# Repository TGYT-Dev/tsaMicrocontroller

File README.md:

a wearable project for TSA microcontroller project

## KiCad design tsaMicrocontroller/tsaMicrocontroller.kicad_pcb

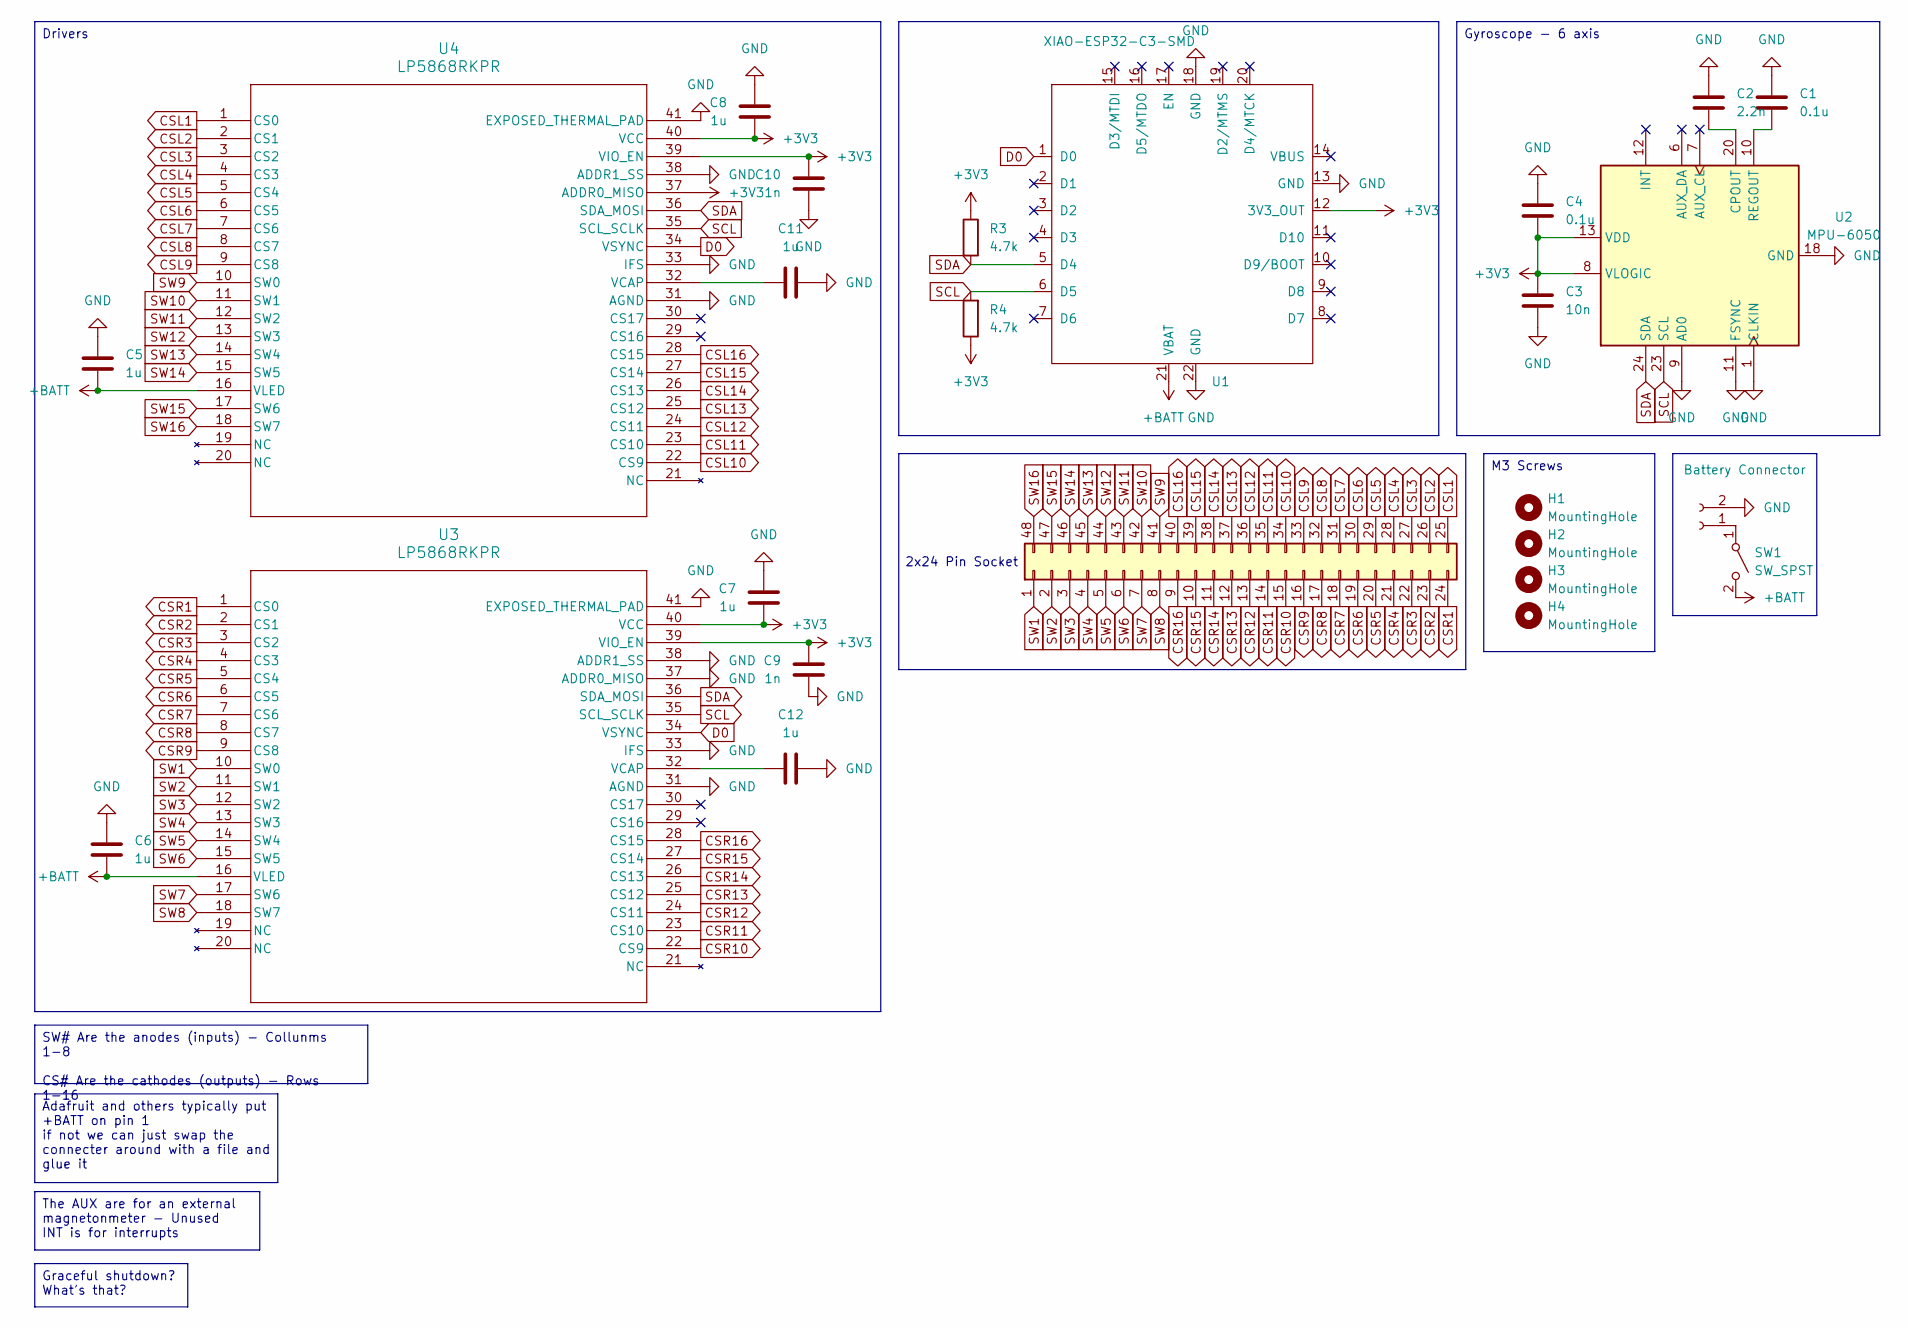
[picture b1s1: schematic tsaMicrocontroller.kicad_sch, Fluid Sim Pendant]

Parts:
C1, C4: 0.1u; C_01005_0402Metric
C2: 2.2n; C_01005_0402Metric
C3: 10n; C_01005_0402Metric
C5, C6, C7, C8, C11, C12: 1u; C_01005_0402Metric
C9, C10: 1n; C_01005_0402Metric
H1, H2, H3, H4: MountingHole; MountingHole_3.2mm_M3
J1: Battery Connector; JST_PH_S2B-PH-K_1x02_P2.00mm_Horizontal
J2: Conn_02x24_Counter_Clockwise; PinSocket_2x24_P2.54mm_Vertical
R3, R4: 4.7k; R_0201_0603Metric_Pad0.64x0.40mm_HandSolder
SW1: SW_SPST; SW_DIP_SPSTx01_Slide_6.7x4.1mm_W6.73mm_P2.54mm_LowProfile_J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
U1: XIAO-ESP32-C3-SMD; MCU_Seeed_ESP32C3
U2: MPU-6050; InvenSense_QFN-24_4x4mm_P0.5mm
U3, U4: LP5868RKPR; VQFN40-RKP_TEX

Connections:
+3V3: C3.1, C4.2, C7.2, C8.2, C9.2, C10.2, R3.1, R4.1, U1.12 (3V3_OUT), U2.8 (VLOGIC), U2.13 (VDD), U3.39 (VIO_EN), U3.40 (VCC), U4.37 (ADDR0_MISO), U4.39 (VIO_EN), U4.40 (VCC)
+BATT: C5.2, C6.2, SW1.2 (B), U1.21 (VBAT), U3.16 (VLED), U4.16 (VLED)
CSL1: J2.25, U4.1 (CS0)
CSL2: J2.26, U4.2 (CS1)
CSL3: J2.27, U4.3 (CS2)
CSL4: J2.28, U4.4 (CS3)
CSL5: J2.29, U4.5 (CS4)
CSL6: J2.30, U4.6 (CS5)
CSL7: J2.31, U4.7 (CS6)
CSL8: J2.32, U4.8 (CS7)
CSL9: J2.33, U4.9 (CS8)
CSL10: J2.34, U4.22 (CS9)
CSL11: J2.35, U4.23 (CS10)
CSL12: J2.36, U4.24 (CS11)
CSL13: J2.37, U4.25 (CS12)
CSL14: J2.38, U4.26 (CS13)
CSL15: J2.39, U4.27 (CS14)
CSL16: J2.40, U4.28 (CS15)
CSR1: J2.24, U3.1 (CS0)
CSR2: J2.23, U3.2 (CS1)
CSR3: J2.22, U3.3 (CS2)
CSR4: J2.21, U3.4 (CS3)
CSR5: J2.20, U3.5 (CS4)
CSR6: J2.19, U3.6 (CS5)
CSR7: J2.18, U3.7 (CS6)
CSR8: J2.17, U3.8 (CS7)
CSR9: J2.16, U3.9 (CS8)
CSR10: J2.15, U3.22 (CS9)
CSR11: J2.14, U3.23 (CS10)
CSR12: J2.13, U3.24 (CS11)
CSR13: J2.12, U3.25 (CS12)
CSR14: J2.11, U3.26 (CS13)
CSR15: J2.10, U3.27 (CS14)
CSR16: J2.9, U3.28 (CS15)
D0: U1.1 (D0), U3.34 (VSYNC), U4.34 (VSYNC)
GND: C1.1, C2.1, C3.2, C4.1, C5.1, C6.1, C7.1, C8.1, C9.1, C10.1, C11.1, C12.1, J1.2, U1.13 (GND), U1.18 (GND), U1.22 (GND), U2.1 (CLKIN), U2.9 (AD0), U2.11 (FSYNC), U2.18 (GND), U3.31 (AGND), U3.33 (IFS), U3.37 (ADDR0_MISO), U3.38 (ADDR1_SS), U3.41 (EXPOSED_THERMAL_PAD), U4.31 (AGND), U4.33 (IFS), U4.38 (ADDR1_SS), U4.41 (EXPOSED_THERMAL_PAD)
unnamed: J1.1, SW1.1 (A)
unnamed: C2.2, U2.20 (CPOUT)
unnamed: C1.2, U2.10 (REGOUT)
unnamed: C12.2, U3.32 (VCAP)
unnamed: C11.2, U4.32 (VCAP)
SCL: R4.2, U1.6 (D5), U2.23 (SCL), U3.35 (SCL_SCLK), U4.35 (SCL_SCLK)
SDA: R3.2, U1.5 (D4), U2.24 (SDA), U3.36 (SDA_MOSI), U4.36 (SDA_MOSI)
SW1: J2.1, U3.10 (SW0)
SW2: J2.2, U3.11 (SW1)
SW3: J2.3, U3.12 (SW2)
SW4: J2.4, U3.13 (SW3)
SW5: J2.5, U3.14 (SW4)
SW6: J2.6, U3.15 (SW5)
SW7: J2.7, U3.17 (SW6)
SW8: J2.8, U3.18 (SW7)
SW9: J2.41, U4.10 (SW0)
SW10: J2.42, U4.11 (SW1)
SW11: J2.43, U4.12 (SW2)
SW12: J2.44, U4.13 (SW3)
SW13: J2.45, U4.14 (SW4)
SW14: J2.46, U4.15 (SW5)
SW15: J2.47, U4.17 (SW6)
SW16: J2.48, U4.18 (SW7)

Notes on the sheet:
2x24 Pin Socket
M3 Screws
Drivers
The AUX are for an external magnetonmeter - Unused INT is for interrupts
SW# Are the anodes (inputs) - Collunms 1-8 CS# Are the cathodes (outputs) - Rows 1-16
Adafruit and others typically put +BATT on pin 1 if not we can just swap the connecter around with a file and glue it
Gyroscope - 6 axis
Graceful shutdown? What's that?

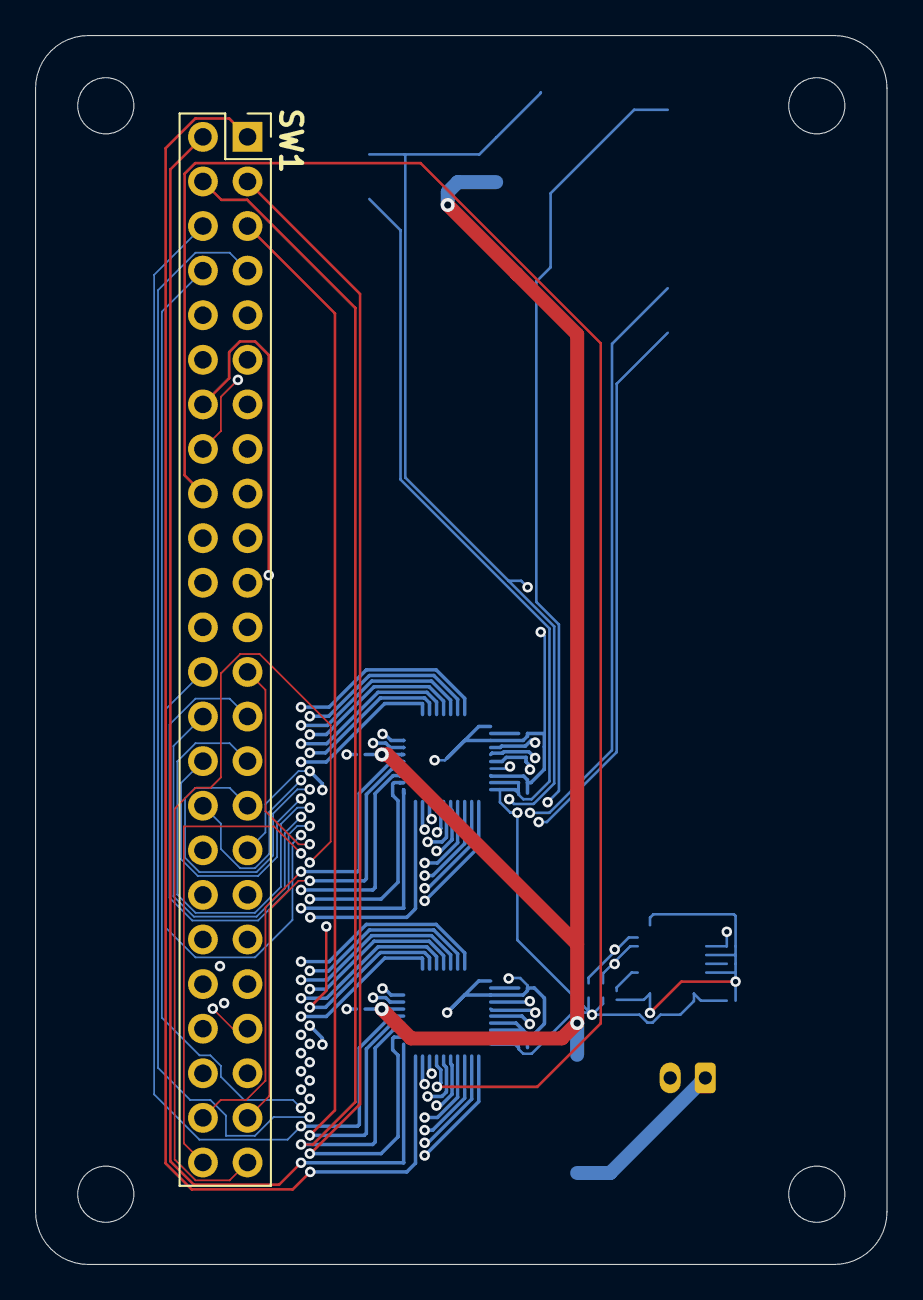
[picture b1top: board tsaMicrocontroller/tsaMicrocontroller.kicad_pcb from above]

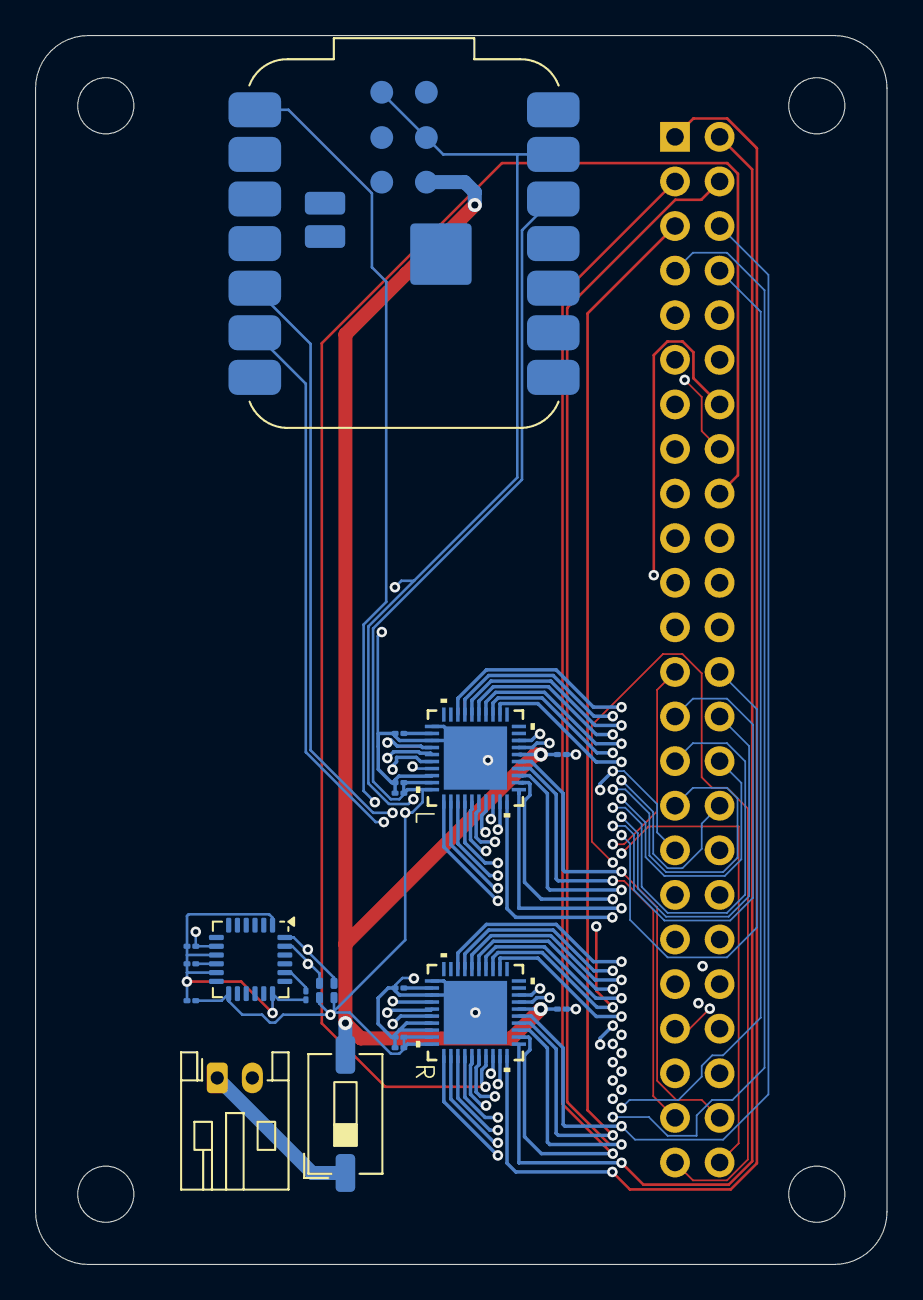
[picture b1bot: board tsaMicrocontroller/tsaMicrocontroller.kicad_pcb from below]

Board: 4 copper layers, 48.5 x 70.0 mm, 25 parts (20 on the bottom side), 59 nets.

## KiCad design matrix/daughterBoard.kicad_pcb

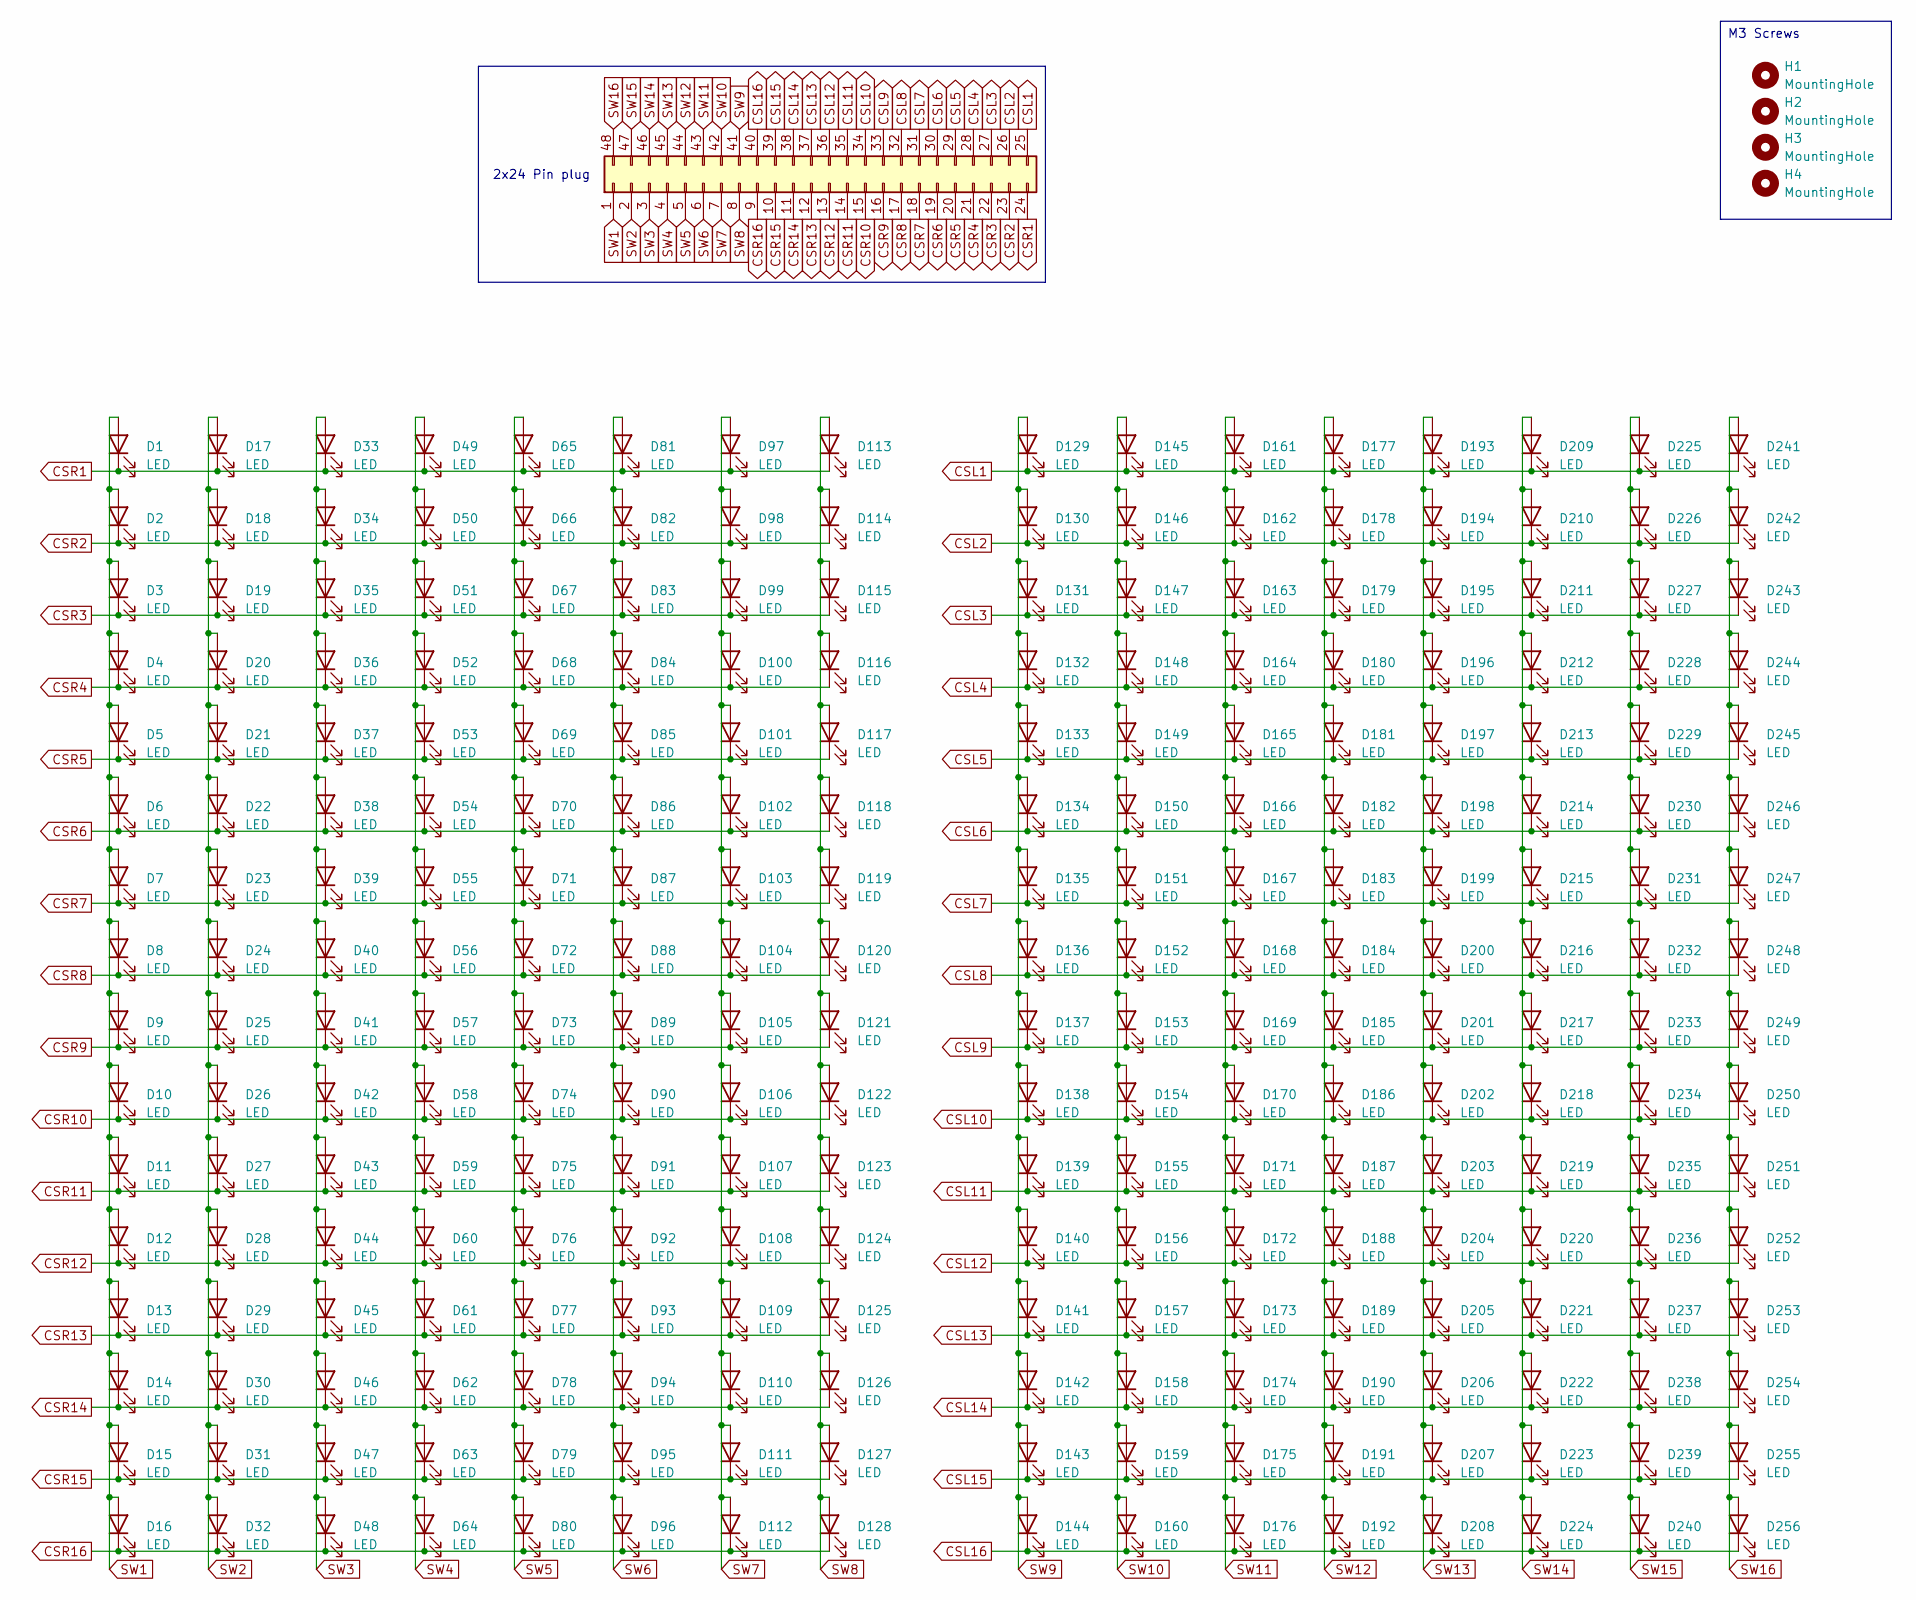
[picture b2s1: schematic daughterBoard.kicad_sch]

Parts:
D1, D2, D3, D4, D5, D6, D7, D8, D9, D10, D11, D12, D13, D14, D15, D16, D17, D18, D19, D20, D21, D22, D23, D24, D25, D26, D27, D28, D29, D30, D31, D32, D33, D34, D35, D36, D37, D38, D39, D40, D41, D42, D43, D44, D45, D46, D47, D48, D49, D50, D51, D52, D53, D54, D55, D56, D57, D58, D59, D60, D61, D62, D63, D64, D65, D66, D67, D68, D69, D70, D71, D72, D73, D74, D75, D76, D77, D78, D79, D80, D81, D82, D83, D84, D85, D86, D87, D88, D89, D90, D91, D92, D93, D94, D95, D96, D97, D98, D99, D100, D101, D102, D103, D104, D105, D106, D107, D108, D109, D110, D111, D112, D113, D114, D115, D116, D117, D118, D119, D120, D121, D122, D123, D124, D125, D126, D127, D128, D129, D130, D131, D132, D133, D134, D135, D136, D137, D138, D139, D140, D141, D142, D143, D144, D145, D146, D147, D148, D149, D150, D151, D152, D153, D154, D155, D156, D157, D158, D159, D160, D161, D162, D163, D164, D165, D166, D167, D168, D169, D170, D171, D172, D173, D174, D175, D176, D177, D178, D179, D180, D181, D182, D183, D184, D185, D186, D187, D188, D189, D190, D191, D192, D193, D194, D195, D196, D197, D198, D199, D200, D201, D202, D203, D204, D205, D206, D207, D208, D209, D210, D211, D212, D213, D214, D215, D216, D217, D218, D219, D220, D221, D222, D223, D224, D225, D226, D227, D228, D229, D230, D231, D232, D233, D234, D235, D236, D237, D238, D239, D240, D241, D242, D243, D244, D245, D246, D247, D248, D249, D250, D251, D252, D253, D254, D255, D256: LED; LED_0603_1608Metric
H1, H2, H3, H4: MountingHole; MountingHole_3.2mm_M3
J1: Conn_02x24_Counter_Clockwise; PinHeader_2x24_P2.54mm_Vertical

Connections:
CSL1: D129.1 (K), D145.1 (K), D161.1 (K), D177.1 (K), D193.1 (K), D209.1 (K), D225.1 (K), D241.1 (K), J1.25
CSL2: D130.1 (K), D146.1 (K), D162.1 (K), D178.1 (K), D194.1 (K), D210.1 (K), D226.1 (K), D242.1 (K), J1.26
CSL3: D131.1 (K), D147.1 (K), D163.1 (K), D179.1 (K), D195.1 (K), D211.1 (K), D227.1 (K), D243.1 (K), J1.27
CSL4: D132.1 (K), D148.1 (K), D164.1 (K), D180.1 (K), D196.1 (K), D212.1 (K), D228.1 (K), D244.1 (K), J1.28
CSL5: D133.1 (K), D149.1 (K), D165.1 (K), D181.1 (K), D197.1 (K), D213.1 (K), D229.1 (K), D245.1 (K), J1.29
CSL6: D134.1 (K), D150.1 (K), D166.1 (K), D182.1 (K), D198.1 (K), D214.1 (K), D230.1 (K), D246.1 (K), J1.30
CSL7: D135.1 (K), D151.1 (K), D167.1 (K), D183.1 (K), D199.1 (K), D215.1 (K), D231.1 (K), D247.1 (K), J1.31
CSL8: D136.1 (K), D152.1 (K), D168.1 (K), D184.1 (K), D200.1 (K), D216.1 (K), D232.1 (K), D248.1 (K), J1.32
CSL9: D137.1 (K), D153.1 (K), D169.1 (K), D185.1 (K), D201.1 (K), D217.1 (K), D233.1 (K), D249.1 (K), J1.33
CSL10: D138.1 (K), D154.1 (K), D170.1 (K), D186.1 (K), D202.1 (K), D218.1 (K), D234.1 (K), D250.1 (K), J1.34
CSL11: D139.1 (K), D155.1 (K), D171.1 (K), D187.1 (K), D203.1 (K), D219.1 (K), D235.1 (K), D251.1 (K), J1.35
CSL12: D140.1 (K), D156.1 (K), D172.1 (K), D188.1 (K), D204.1 (K), D220.1 (K), D236.1 (K), D252.1 (K), J1.36
CSL13: D141.1 (K), D157.1 (K), D173.1 (K), D189.1 (K), D205.1 (K), D221.1 (K), D237.1 (K), D253.1 (K), J1.37
CSL14: D142.1 (K), D158.1 (K), D174.1 (K), D190.1 (K), D206.1 (K), D222.1 (K), D238.1 (K), D254.1 (K), J1.38
CSL15: D143.1 (K), D159.1 (K), D175.1 (K), D191.1 (K), D207.1 (K), D223.1 (K), D239.1 (K), D255.1 (K), J1.39
CSL16: D144.1 (K), D160.1 (K), D176.1 (K), D192.1 (K), D208.1 (K), D224.1 (K), D240.1 (K), D256.1 (K), J1.40
CSR1: D1.1 (K), D17.1 (K), D33.1 (K), D49.1 (K), D65.1 (K), D81.1 (K), D97.1 (K), D113.1 (K), J1.24
CSR2: D2.1 (K), D18.1 (K), D34.1 (K), D50.1 (K), D66.1 (K), D82.1 (K), D98.1 (K), D114.1 (K), J1.23
CSR3: D3.1 (K), D19.1 (K), D35.1 (K), D51.1 (K), D67.1 (K), D83.1 (K), D99.1 (K), D115.1 (K), J1.22
CSR4: D4.1 (K), D20.1 (K), D36.1 (K), D52.1 (K), D68.1 (K), D84.1 (K), D100.1 (K), D116.1 (K), J1.21
CSR5: D5.1 (K), D21.1 (K), D37.1 (K), D53.1 (K), D69.1 (K), D85.1 (K), D101.1 (K), D117.1 (K), J1.20
CSR6: D6.1 (K), D22.1 (K), D38.1 (K), D54.1 (K), D70.1 (K), D86.1 (K), D102.1 (K), D118.1 (K), J1.19
CSR7: D7.1 (K), D23.1 (K), D39.1 (K), D55.1 (K), D71.1 (K), D87.1 (K), D103.1 (K), D119.1 (K), J1.18
CSR8: D8.1 (K), D24.1 (K), D40.1 (K), D56.1 (K), D72.1 (K), D88.1 (K), D104.1 (K), D120.1 (K), J1.17
CSR9: D9.1 (K), D25.1 (K), D41.1 (K), D57.1 (K), D73.1 (K), D89.1 (K), D105.1 (K), D121.1 (K), J1.16
CSR10: D10.1 (K), D26.1 (K), D42.1 (K), D58.1 (K), D74.1 (K), D90.1 (K), D106.1 (K), D122.1 (K), J1.15
CSR11: D11.1 (K), D27.1 (K), D43.1 (K), D59.1 (K), D75.1 (K), D91.1 (K), D107.1 (K), D123.1 (K), J1.14
CSR12: D12.1 (K), D28.1 (K), D44.1 (K), D60.1 (K), D76.1 (K), D92.1 (K), D108.1 (K), D124.1 (K), J1.13
CSR13: D13.1 (K), D29.1 (K), D45.1 (K), D61.1 (K), D77.1 (K), D93.1 (K), D109.1 (K), D125.1 (K), J1.12
CSR14: D14.1 (K), D30.1 (K), D46.1 (K), D62.1 (K), D78.1 (K), D94.1 (K), D110.1 (K), D126.1 (K), J1.11
CSR15: D15.1 (K), D31.1 (K), D47.1 (K), D63.1 (K), D79.1 (K), D95.1 (K), D111.1 (K), D127.1 (K), J1.10
CSR16: D16.1 (K), D32.1 (K), D48.1 (K), D64.1 (K), D80.1 (K), D96.1 (K), D112.1 (K), D128.1 (K), J1.9
SW1: D1.2 (A), D2.2 (A), D3.2 (A), D4.2 (A), D5.2 (A), D6.2 (A), D7.2 (A), D8.2 (A), D9.2 (A), D10.2 (A), D11.2 (A), D12.2 (A), D13.2 (A), D14.2 (A), D15.2 (A), D16.2 (A), J1.1
SW2: D17.2 (A), D18.2 (A), D19.2 (A), D20.2 (A), D21.2 (A), D22.2 (A), D23.2 (A), D24.2 (A), D25.2 (A), D26.2 (A), D27.2 (A), D28.2 (A), D29.2 (A), D30.2 (A), D31.2 (A), D32.2 (A), J1.2
SW3: D33.2 (A), D34.2 (A), D35.2 (A), D36.2 (A), D37.2 (A), D38.2 (A), D39.2 (A), D40.2 (A), D41.2 (A), D42.2 (A), D43.2 (A), D44.2 (A), D45.2 (A), D46.2 (A), D47.2 (A), D48.2 (A), J1.3
SW4: D49.2 (A), D50.2 (A), D51.2 (A), D52.2 (A), D53.2 (A), D54.2 (A), D55.2 (A), D56.2 (A), D57.2 (A), D58.2 (A), D59.2 (A), D60.2 (A), D61.2 (A), D62.2 (A), D63.2 (A), D64.2 (A), J1.4
SW5: D65.2 (A), D66.2 (A), D67.2 (A), D68.2 (A), D69.2 (A), D70.2 (A), D71.2 (A), D72.2 (A), D73.2 (A), D74.2 (A), D75.2 (A), D76.2 (A), D77.2 (A), D78.2 (A), D79.2 (A), D80.2 (A), J1.5
SW6: D81.2 (A), D82.2 (A), D83.2 (A), D84.2 (A), D85.2 (A), D86.2 (A), D87.2 (A), D88.2 (A), D89.2 (A), D90.2 (A), D91.2 (A), D92.2 (A), D93.2 (A), D94.2 (A), D95.2 (A), D96.2 (A), J1.6
SW7: D97.2 (A), D98.2 (A), D99.2 (A), D100.2 (A), D101.2 (A), D102.2 (A), D103.2 (A), D104.2 (A), D105.2 (A), D106.2 (A), D107.2 (A), D108.2 (A), D109.2 (A), D110.2 (A), D111.2 (A), D112.2 (A), J1.7
SW8: D113.2 (A), D114.2 (A), D115.2 (A), D116.2 (A), D117.2 (A), D118.2 (A), D119.2 (A), D120.2 (A), D121.2 (A), D122.2 (A), D123.2 (A), D124.2 (A), D125.2 (A), D126.2 (A), D127.2 (A), D128.2 (A), J1.8
SW9: D129.2 (A), D130.2 (A), D131.2 (A), D132.2 (A), D133.2 (A), D134.2 (A), D135.2 (A), D136.2 (A), D137.2 (A), D138.2 (A), D139.2 (A), D140.2 (A), D141.2 (A), D142.2 (A), D143.2 (A), D144.2 (A), J1.41
SW10: D145.2 (A), D146.2 (A), D147.2 (A), D148.2 (A), D149.2 (A), D150.2 (A), D151.2 (A), D152.2 (A), D153.2 (A), D154.2 (A), D155.2 (A), D156.2 (A), D157.2 (A), D158.2 (A), D159.2 (A), D160.2 (A), J1.42
SW11: D161.2 (A), D162.2 (A), D163.2 (A), D164.2 (A), D165.2 (A), D166.2 (A), D167.2 (A), D168.2 (A), D169.2 (A), D170.2 (A), D171.2 (A), D172.2 (A), D173.2 (A), D174.2 (A), D175.2 (A), D176.2 (A), J1.43
SW12: D177.2 (A), D178.2 (A), D179.2 (A), D180.2 (A), D181.2 (A), D182.2 (A), D183.2 (A), D184.2 (A), D185.2 (A), D186.2 (A), D187.2 (A), D188.2 (A), D189.2 (A), D190.2 (A), D191.2 (A), D192.2 (A), J1.44
SW13: D193.2 (A), D194.2 (A), D195.2 (A), D196.2 (A), D197.2 (A), D198.2 (A), D199.2 (A), D200.2 (A), D201.2 (A), D202.2 (A), D203.2 (A), D204.2 (A), D205.2 (A), D206.2 (A), D207.2 (A), D208.2 (A), J1.45
SW14: D209.2 (A), D210.2 (A), D211.2 (A), D212.2 (A), D213.2 (A), D214.2 (A), D215.2 (A), D216.2 (A), D217.2 (A), D218.2 (A), D219.2 (A), D220.2 (A), D221.2 (A), D222.2 (A), D223.2 (A), D224.2 (A), J1.46
SW15: D225.2 (A), D226.2 (A), D227.2 (A), D228.2 (A), D229.2 (A), D230.2 (A), D231.2 (A), D232.2 (A), D233.2 (A), D234.2 (A), D235.2 (A), D236.2 (A), D237.2 (A), D238.2 (A), D239.2 (A), D240.2 (A), J1.47
SW16: D241.2 (A), D242.2 (A), D243.2 (A), D244.2 (A), D245.2 (A), D246.2 (A), D247.2 (A), D248.2 (A), D249.2 (A), D250.2 (A), D251.2 (A), D252.2 (A), D253.2 (A), D254.2 (A), D255.2 (A), D256.2 (A), J1.48

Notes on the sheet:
2x24 Pin plug
M3 Screws

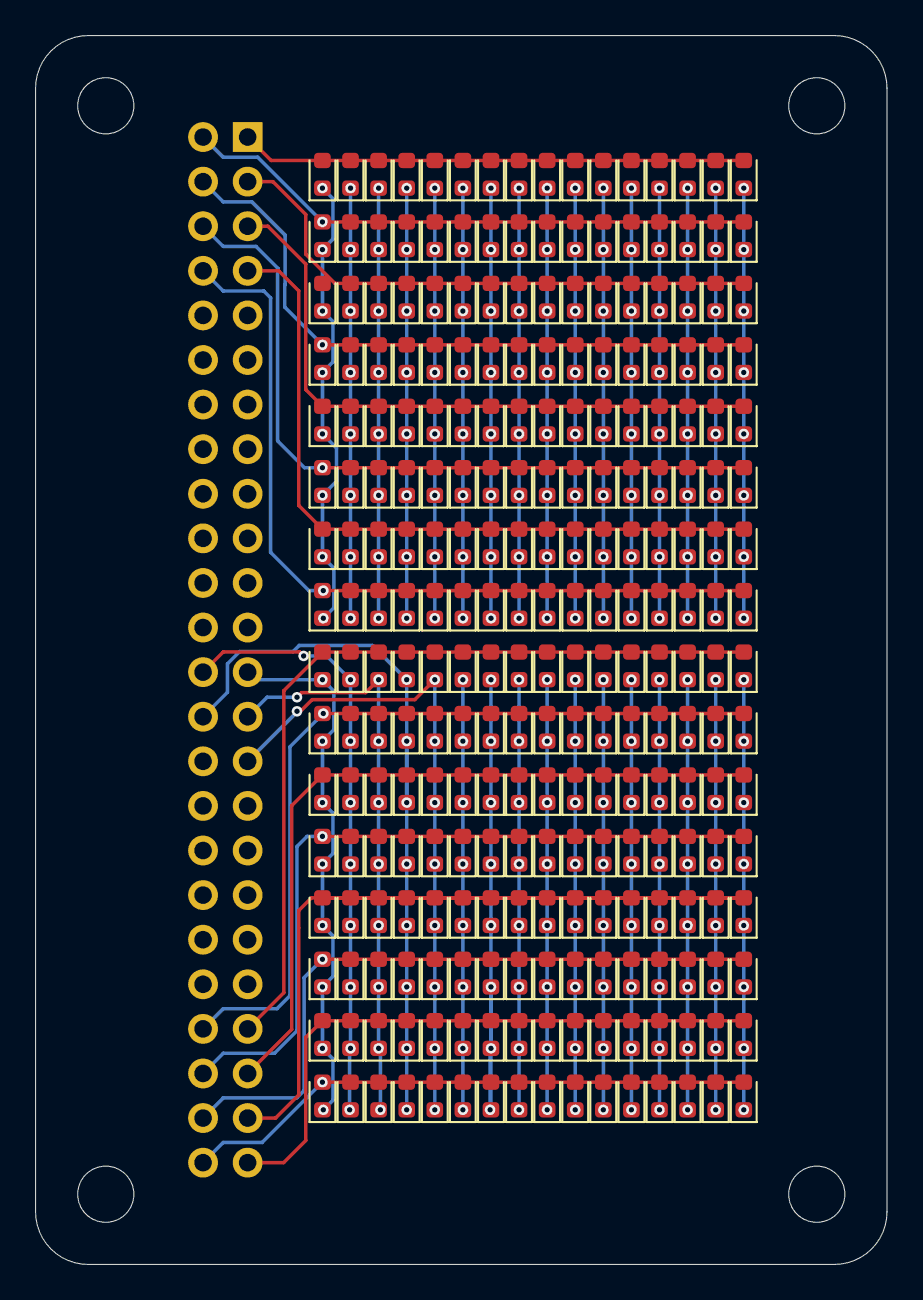
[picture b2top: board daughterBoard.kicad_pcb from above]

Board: 4 copper layers, 48.5 x 70.0 mm, 261 parts (1 on the bottom side), 48 nets.
